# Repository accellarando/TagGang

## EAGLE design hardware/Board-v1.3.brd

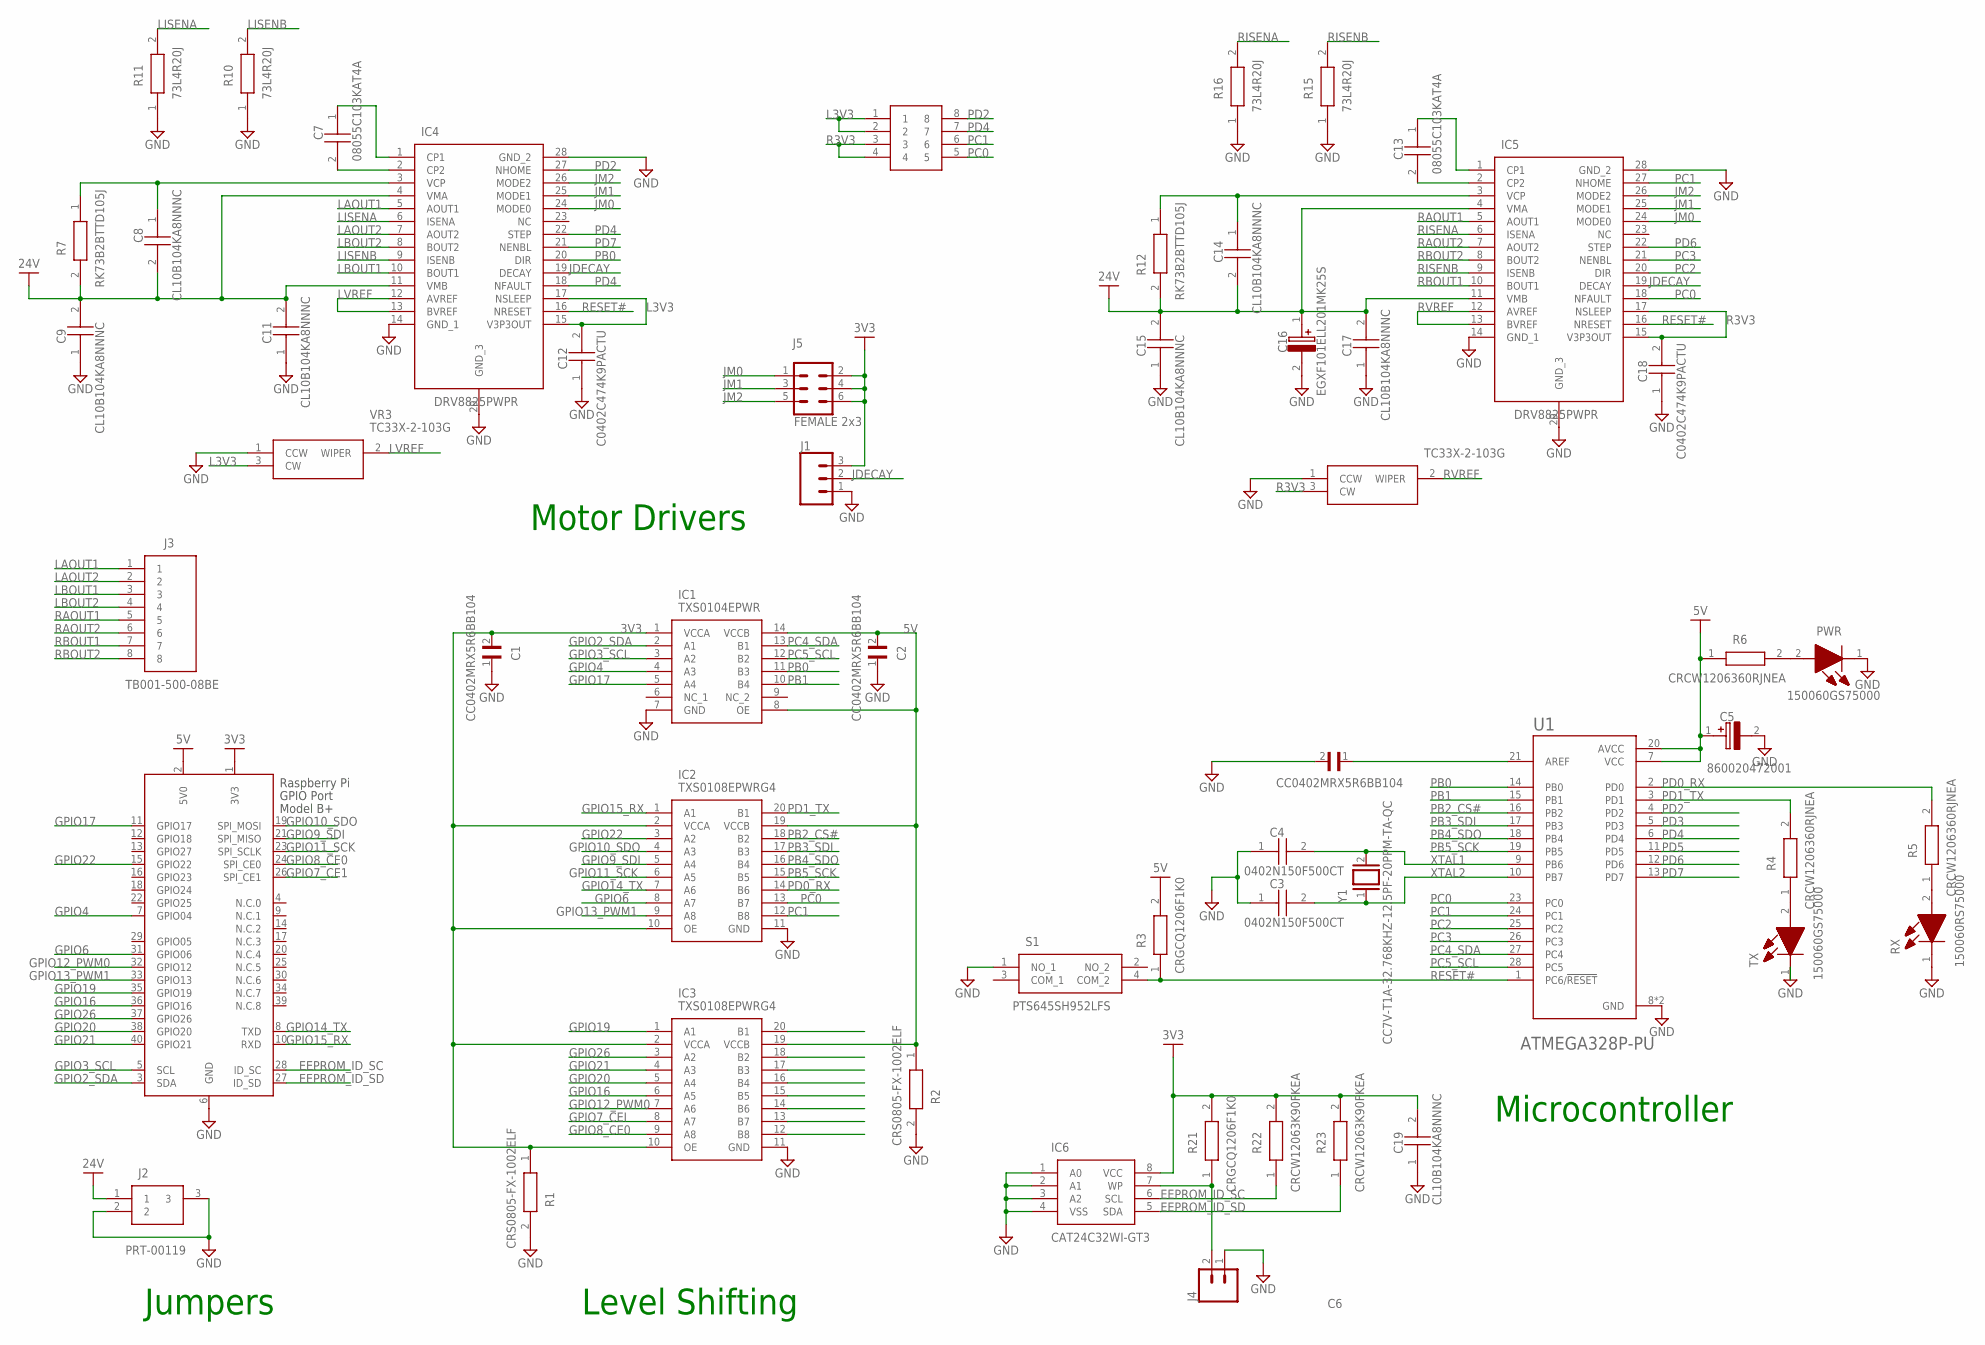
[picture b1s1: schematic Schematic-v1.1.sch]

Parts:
C1, C2, C6: CC0402MRX5R6BB104; CAPC1005X55N
C3, C4: 0402N150F500CT; CAPC1005X55N
C5: 860020472001; CAPPRD200W52D500H1250
C7, C13: 08055C103KAT4A; CAPC2012X94N
C8, C9, C11, C14, C15, C17, C19: CL10B104KA8NNNC; CAPC1608X90N
C12, C18: C0402C474K9PACTU; CAPC1005X55N
C16: EGXF101ELL201MK25S; CAPPRD500W60D1275H2650
IC1: TXS0104EPWR; SOP65P640X120-14N
IC2, IC3: TXS0108EPWRG4; SOP65P640X120-20N
IC4, IC5: DRV8825PWPR; SOP65P640X120-29N
IC6: CAT24C32WI-GT3; SOIC127P600X175-8N
J1: CONN_03; 1X03
J2: PRT-00119; PRT00119
J3: TB001-500-08BE; TB00150008BE
J4: CONN_02; 1X02
J5: FEMALE 2x3; 2X3
PWR: 150060GS75000; LEDC1608X80N
R1, R2: CRS0805-FX-1002ELF; RESC2012X60N
R3, R21: CRGCQ1206F1K0; RESC3116X65N
R4, R5, R6: CRCW1206360RJNEA; RESC3216X60N
R7, R12: RK73B2BTTD105J; RESC3216X70N
R10, R11, R15, R16: 73L4R20J; RESC3216X70N
R22, R23: CRCW12063K90FKEA; RESC3216X60N
RN1: YC124-JR-0710KL; YC124JR0710KL
RX: 150060RS75000; LEDC1608X80N
S1: PTS645SH952LFS
TX: 150060GS75000; LEDC1608X80N
U1: ATMEGA328P-PU; DIP794W46P254L2967H457Q28B
VR3, VR4: TC33X-2-103G; TC33X2503E
X1: RASPI_BOARD_B+_HD; RASPI_BOARD_B+HAT_DF
Y1: CC7V-T1A-32.768KHZ-12.5PF-20PPM-TA-QC; XTAL_CC7V-T1A-32.768KHZ-12.5PF-20PPM-TA-QC

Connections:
24V: C8.2, C9.2, C11.2, C14.2, C15.2, C16.1 (+), C17.2, IC4.4 (VMA), IC4.11 (VMB), IC5.4 (VMA), IC5.11 (VMB), J2.1, R7.2, R12.2
EEPROM_ID_SC: IC6.6 (SCL), R22.1, X1.28 (ID_SC)
EEPROM_ID_SD: IC6.5 (SDA), R23.1, X1.27 (ID_SD)
GND: C1.1, C2.1, C3.1, C4.1, C5.2 (-), C6.2, C9.1, C11.1, C12.1, C15.1, C16.2 (-), C17.1, C18.1, C19.1, IC1.7 (GND), IC2.11 (GND), IC3.11 (GND), IC4.14 (GND_1), IC4.28 (GND_2), IC4.29 (GND_3), IC5.14 (GND_1), IC5.28 (GND_2), IC5.29 (GND_3), IC6.1 (A0), IC6.2 (A1), IC6.3 (A2), IC6.4 (VSS), J1.1, J2.2, J2.3, J4.1, PWR.1 (K), R1.2, R2.2, R10.1, R11.1, R15.1, R16.1, RX.1 (K), S1.1 (NO_1), TX.1 (K), U1.8 (GND), U1.22 (GND), VR3.1 (CCW), VR4.1 (CCW), X1.6 (GND); also elsewhere on the board
GPIO2_SDA: IC1.2 (A1), X1.3 (SDA)
GPIO3_SCL: IC1.3 (A2), X1.5 (SCL)
GPIO4: IC1.4 (A3), X1.7 (GPIO04)
GPIO6: IC2.8 (A7), X1.31 (GPIO06)
GPIO7_CE1: X1.26 (SPI_CE1)
GPIO7_CEI: IC3.8 (A7)
GPIO8_CE0: IC3.9 (A8), X1.24 (SPI_CE0)
GPIO9_SDI: IC2.5 (A4), X1.21 (SPI_MISO)
GPIO10_SDO: IC2.4 (A3), X1.19 (SPI_MOSI)
GPIO11_SCK: IC2.6 (A5), X1.23 (SPI_SCLK)
GPIO12_PWM0: IC3.7 (A6), X1.32 (GPIO12)
GPIO13_PWM1: IC2.9 (A8), X1.33 (GPIO13)
GPIO14_TX: IC2.7 (A6), X1.8 (TXD)
GPIO15_RX: IC2.1 (A1), X1.10 (RXD)
GPIO16: IC3.6 (A5), X1.36 (GPIO16)
GPIO17: IC1.5 (A4), X1.11 (GPIO17)
GPIO19: IC3.1 (A1), X1.35 (GPIO19)
GPIO20: IC3.5 (A4), X1.38 (GPIO20)
GPIO21: IC3.4 (A3), X1.40 (GPIO21)
GPIO22: IC2.3 (A2), X1.15 (GPIO22)
GPIO26: IC3.3 (A2), X1.37 (GPIO26)
JDECAY: IC4.19 (DECAY), IC5.19 (DECAY), J1.2; also elsewhere on the board
JM2: IC4.26 (MODE2), IC5.26 (MODE2), J5.5; also elsewhere on the board
L3V3: C12.2, IC4.15 (V3P3OUT), IC4.17 (NSLEEP), RN1.1, RN1.2, VR3.3 (CW)
LAOUT1: IC4.5 (AOUT1), J3.1
LAOUT2: IC4.7 (AOUT2), J3.2
LBOUT1: IC4.10 (BOUT1), J3.3
LBOUT2: IC4.8 (BOUT2), J3.4
LISENA: IC4.6 (ISENA), R11.2
LISENB: IC4.9 (ISENB), R10.2
LVREF: IC4.12 (AVREF), IC4.13 (BVREF), VR3.2 (WIPER)
unnamed: C13.1, IC5.1 (CP1)
unnamed: R5.1, RX.2 (A)
unnamed: PWR.2 (A), R6.2
unnamed: C6.1, U1.21 (AREF)
unnamed: C7.1, IC4.1 (CP1)
unnamed: C7.2, IC4.2 (CP2)
unnamed: C13.2, IC5.2 (CP2)
unnamed: C8.1, IC4.3 (VCP), R7.1
unnamed: C14.1, IC5.3 (VCP), R12.1
unnamed: R4.1, TX.2 (A)
unnamed: IC6.7 (WP), J4.2, R21.1
PB0: IC1.11 (B3), IC4.20 (DIR), U1.14 (PB0)
PB1: IC1.10 (B4), U1.15 (PB1)
PB2_CS#: IC2.18 (B2), U1.16 (PB2)
PB3_SDI: IC2.17 (B3), U1.17 (PB3)
PB4_SDO: IC2.16 (B4), U1.18 (PB4)
PB5_SCK: IC2.15 (B5), U1.19 (PB5)
PC2: IC5.20 (DIR), U1.25 (PC2)
PC3: IC5.21 (NENBL), U1.26 (PC3)
PC4_SDA: IC1.13 (B1), U1.27 (PC4)
PC5_SCL: IC1.12 (B2), U1.28 (PC5)
PD0_RX: IC2.14 (B6), R5.2, U1.2 (PD0)
PD1_TX: IC2.20 (B1), R4.2, U1.3 (PD1)
PD3: U1.5 (PD3)
PD5: U1.11 (PD5)
PD6: IC5.22 (STEP), U1.12 (PD6)
PD7: IC4.21 (NENBL), U1.13 (PD7)
R3V3: C18.2, IC5.15 (V3P3OUT), IC5.17 (NSLEEP), RN1.3, RN1.4, VR4.3 (CW)
RAOUT1: IC5.5 (AOUT1), J3.5
RAOUT2: IC5.7 (AOUT2), J3.6
RBOUT1: IC5.10 (BOUT1), J3.7
RBOUT2: IC5.8 (BOUT2), J3.8
RESET#: IC4.16 (NRESET), IC5.16 (NRESET), R3.1, S1.4 (COM_2), U1.1 (PC6/!RESET)
RISENA: IC5.6 (ISENA), R16.2
RISENB: IC5.9 (ISENB), R15.2
RVREF: IC5.12 (AVREF), IC5.13 (BVREF), VR4.2 (WIPER)
XTAL1: C4.2, U1.9 (PB6), Y1.2
XTAL2: C3.2, U1.10 (PB7), Y1.1

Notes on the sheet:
Jumpers
Level Shifting
Microcontroller
Motor Drivers

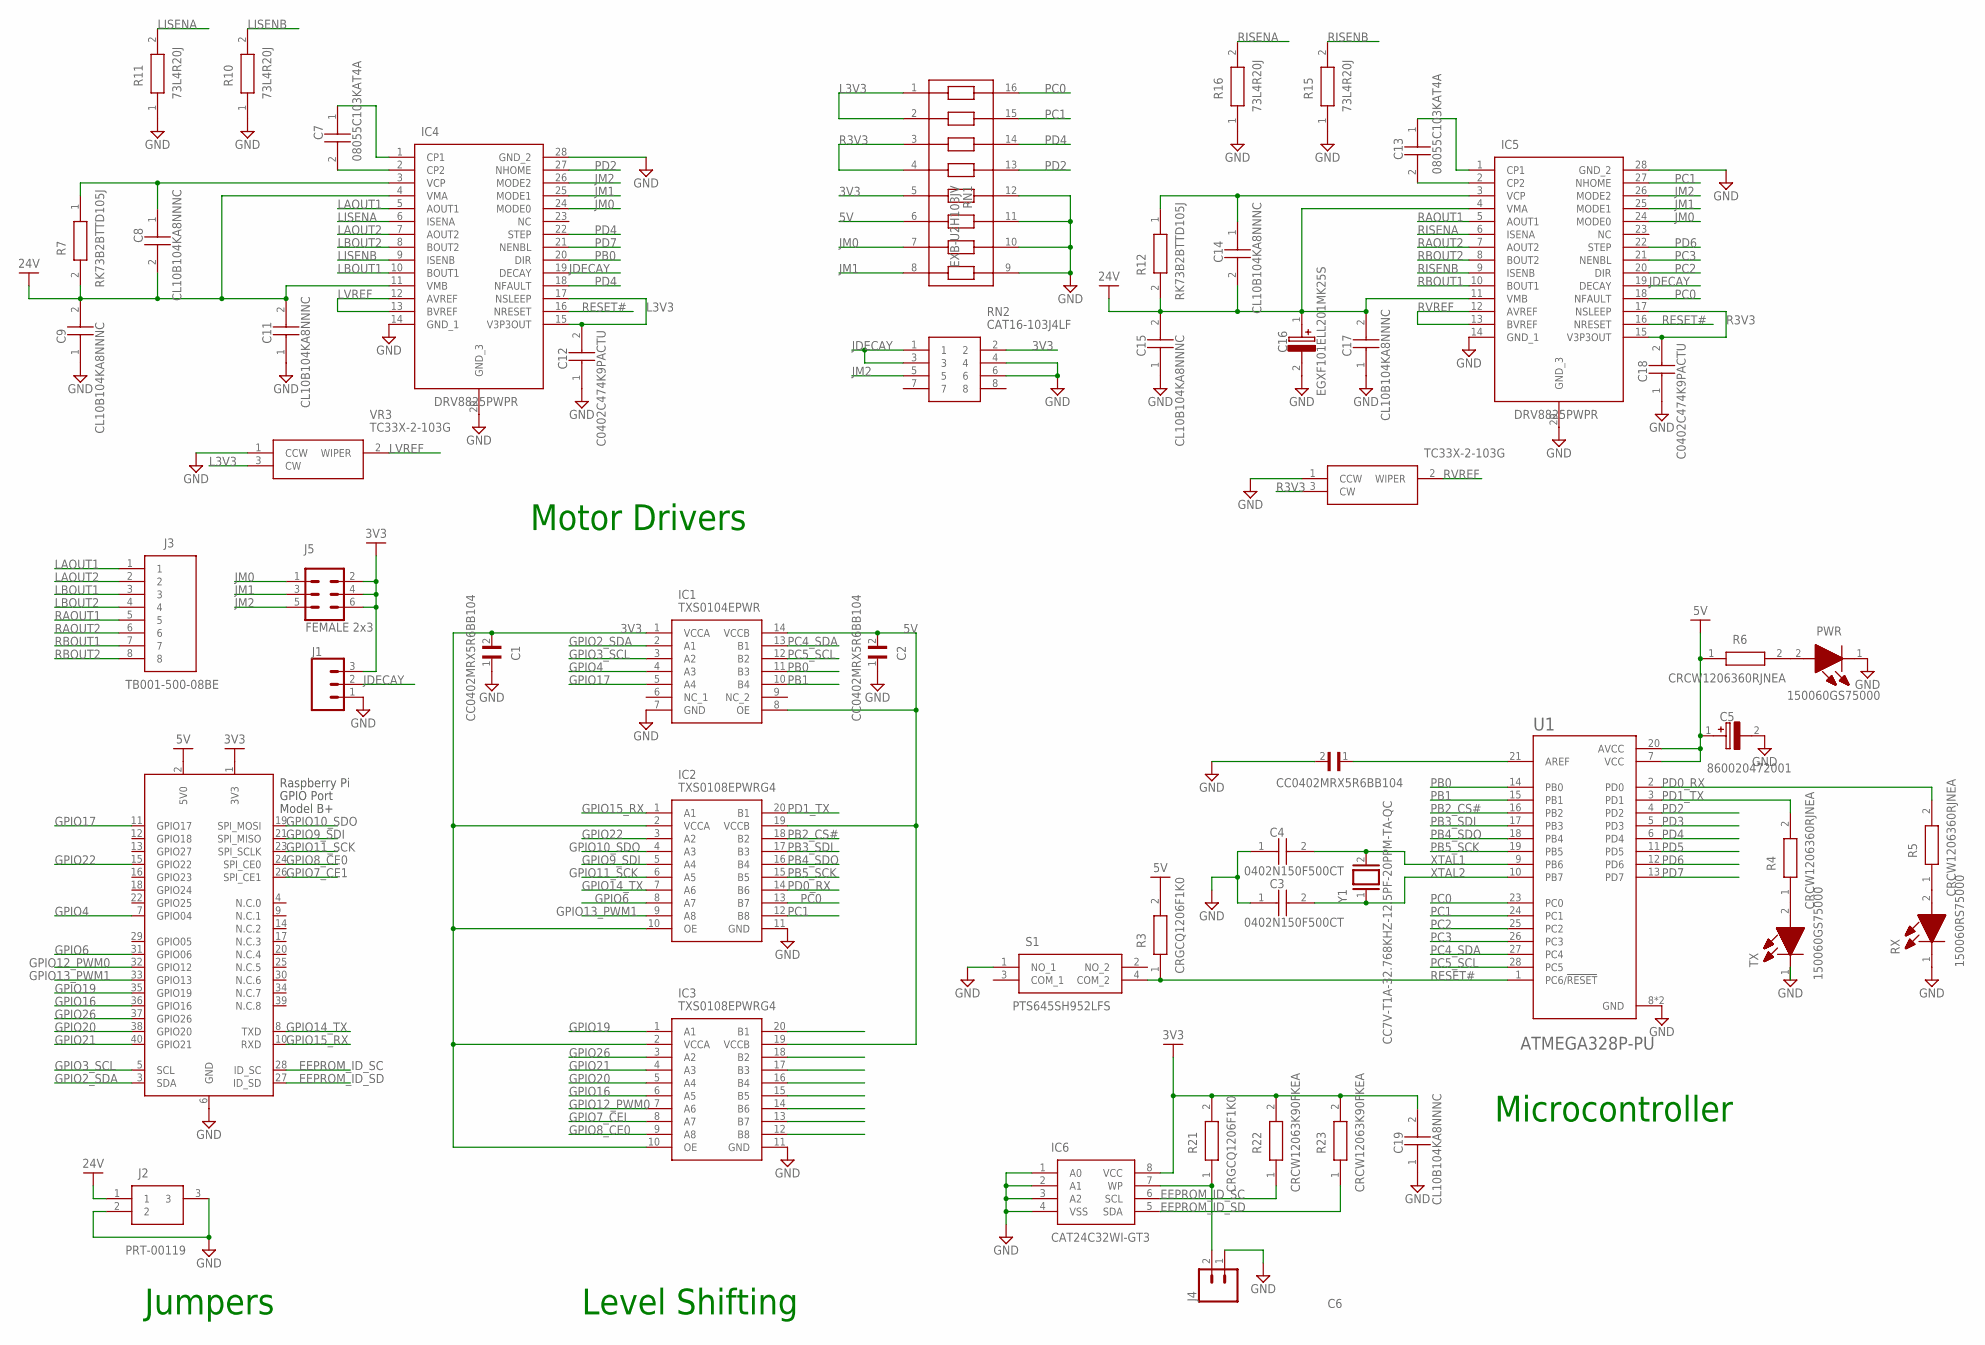
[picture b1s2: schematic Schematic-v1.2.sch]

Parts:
C1, C2, C6: CC0402MRX5R6BB104; CAPC1005X55N
C3, C4: 0402N150F500CT; CAPC1005X55N
C5: 860020472001; CAPPRD200W52D500H1250
C7, C13: 08055C103KAT4A; CAPC2012X94N
C8, C9, C11, C14, C15, C17, C19: CL10B104KA8NNNC; CAPC1608X90N
C12, C18: C0402C474K9PACTU; CAPC1005X55N
C16: EGXF101ELL201MK25S; CAPPRD500W60D1275H2650
IC1: TXS0104EPWR; SOP65P640X120-14N
IC2, IC3: TXS0108EPWRG4; SOP65P640X120-20N
IC4, IC5: DRV8825PWPR; SOP65P640X120-29N
IC6: CAT24C32WI-GT3; SOIC127P600X175-8N
J1: CONN_03; 1X03
J2: PRT-00119; PRT00119
J3: TB001-500-08BE; TB00150008BE
J4: CONN_02; 1X02
J5: FEMALE 2x3; 2X3
PWR: 150060GS75000; LEDC1608X80N
R3, R21: CRGCQ1206F1K0; RESC3116X65N
R4, R5, R6: CRCW1206360RJNEA; RESC3216X60N
R7, R12: RK73B2BTTD105J; RESC3216X70N
R10, R11, R15, R16: 73L4R20J; RESC3216X70N
R22, R23: CRCW12063K90FKEA; RESC3216X60N
RN1: EXB-U2H103JV; EXBU2H
RN2: CAT16-103J4LF; CAPCAV80P155X320X60-8L
RX: 150060RS75000; LEDC1608X80N
S1: PTS645SH952LFS
TX: 150060GS75000; LEDC1608X80N
U1: ATMEGA328P-PU; DIP794W46P254L2967H457Q28B
VR3, VR4: TC33X-2-103G; TC33X2503E
X1: RASPI_BOARD_B+_HD; RASPI_BOARD_B+HAT_DF
Y1: CC7V-T1A-32.768KHZ-12.5PF-20PPM-TA-QC; XTAL_CC7V-T1A-32.768KHZ-12.5PF-20PPM-TA-QC

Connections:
24V: C8.2, C9.2, C11.2, C14.2, C15.2, C16.1 (+), C17.2, IC4.4 (VMA), IC4.11 (VMB), IC5.4 (VMA), IC5.11 (VMB), J2.1, R7.2, R12.2
EEPROM_ID_SC: IC6.6 (SCL), R22.1, X1.28 (ID_SC)
EEPROM_ID_SD: IC6.5 (SDA), R23.1, X1.27 (ID_SD)
GND: C1.1, C2.1, C3.1, C4.1, C5.2 (-), C6.2, C9.1, C11.1, C12.1, C15.1, C16.2 (-), C17.1, C18.1, C19.1, IC1.7 (GND), IC2.11 (GND), IC3.11 (GND), IC4.14 (GND_1), IC4.28 (GND_2), IC4.29 (GND_3), IC5.14 (GND_1), IC5.28 (GND_2), IC5.29 (GND_3), IC6.1 (A0), IC6.2 (A1), IC6.3 (A2), IC6.4 (VSS), J1.1, J2.2, J2.3, J4.1, PWR.1 (K), R10.1, R11.1, R15.1, R16.1, RN1.9, RN1.10, RN1.11, RN1.12, RN2.4, RN2.6, RX.1 (K), S1.1 (NO_1), TX.1 (K), U1.8 (GND), U1.22 (GND), VR3.1 (CCW), VR4.1 (CCW), X1.6 (GND); also elsewhere on the board
GPIO2_SDA: IC1.2 (A1), X1.3 (SDA)
GPIO3_SCL: IC1.3 (A2), X1.5 (SCL)
GPIO4: IC1.4 (A3), X1.7 (GPIO04)
GPIO6: IC2.8 (A7), X1.31 (GPIO06)
GPIO7_CE1: X1.26 (SPI_CE1)
GPIO7_CEI: IC3.8 (A7)
GPIO8_CE0: IC3.9 (A8), X1.24 (SPI_CE0)
GPIO9_SDI: IC2.5 (A4), X1.21 (SPI_MISO)
GPIO10_SDO: IC2.4 (A3), X1.19 (SPI_MOSI)
GPIO11_SCK: IC2.6 (A5), X1.23 (SPI_SCLK)
GPIO12_PWM0: IC3.7 (A6), X1.32 (GPIO12)
GPIO13_PWM1: IC2.9 (A8), X1.33 (GPIO13)
GPIO14_TX: IC2.7 (A6), X1.8 (TXD)
GPIO15_RX: IC2.1 (A1), X1.10 (RXD)
GPIO16: IC3.6 (A5), X1.36 (GPIO16)
GPIO17: IC1.5 (A4), X1.11 (GPIO17)
GPIO19: IC3.1 (A1), X1.35 (GPIO19)
GPIO20: IC3.5 (A4), X1.38 (GPIO20)
GPIO21: IC3.4 (A3), X1.40 (GPIO21)
GPIO22: IC2.3 (A2), X1.15 (GPIO22)
GPIO26: IC3.3 (A2), X1.37 (GPIO26)
JDECAY: IC4.19 (DECAY), IC5.19 (DECAY), J1.2, RN2.1, RN2.3
JM2: IC4.26 (MODE2), IC5.26 (MODE2), J5.5, RN2.5
L3V3: C12.2, IC4.15 (V3P3OUT), IC4.17 (NSLEEP), RN1.1, RN1.2, VR3.3 (CW)
LAOUT1: IC4.5 (AOUT1), J3.1
LAOUT2: IC4.7 (AOUT2), J3.2
LBOUT1: IC4.10 (BOUT1), J3.3
LBOUT2: IC4.8 (BOUT2), J3.4
LISENA: IC4.6 (ISENA), R11.2
LISENB: IC4.9 (ISENB), R10.2
LVREF: IC4.12 (AVREF), IC4.13 (BVREF), VR3.2 (WIPER)
unnamed: C13.1, IC5.1 (CP1)
unnamed: R5.1, RX.2 (A)
unnamed: PWR.2 (A), R6.2
unnamed: C6.1, U1.21 (AREF)
unnamed: C7.1, IC4.1 (CP1)
unnamed: C7.2, IC4.2 (CP2)
unnamed: C13.2, IC5.2 (CP2)
unnamed: C8.1, IC4.3 (VCP), R7.1
unnamed: C14.1, IC5.3 (VCP), R12.1
unnamed: R4.1, TX.2 (A)
unnamed: IC6.7 (WP), J4.2, R21.1
PB0: IC1.11 (B3), IC4.20 (DIR), U1.14 (PB0)
PB1: IC1.10 (B4), U1.15 (PB1)
PB2_CS#: IC2.18 (B2), U1.16 (PB2)
PB3_SDI: IC2.17 (B3), U1.17 (PB3)
PB4_SDO: IC2.16 (B4), U1.18 (PB4)
PB5_SCK: IC2.15 (B5), U1.19 (PB5)
PC2: IC5.20 (DIR), U1.25 (PC2)
PC3: IC5.21 (NENBL), U1.26 (PC3)
PC4_SDA: IC1.13 (B1), U1.27 (PC4)
PC5_SCL: IC1.12 (B2), U1.28 (PC5)
PD0_RX: IC2.14 (B6), R5.2, U1.2 (PD0)
PD1_TX: IC2.20 (B1), R4.2, U1.3 (PD1)
PD3: U1.5 (PD3)
PD5: U1.11 (PD5)
PD6: IC5.22 (STEP), U1.12 (PD6)
PD7: IC4.21 (NENBL), U1.13 (PD7)
R3V3: C18.2, IC5.15 (V3P3OUT), IC5.17 (NSLEEP), RN1.3, RN1.4, VR4.3 (CW)
RAOUT1: IC5.5 (AOUT1), J3.5
RAOUT2: IC5.7 (AOUT2), J3.6
RBOUT1: IC5.10 (BOUT1), J3.7
RBOUT2: IC5.8 (BOUT2), J3.8
RESET#: IC4.16 (NRESET), IC5.16 (NRESET), R3.1, S1.4 (COM_2), U1.1 (PC6/!RESET)
RISENA: IC5.6 (ISENA), R16.2
RISENB: IC5.9 (ISENB), R15.2
RVREF: IC5.12 (AVREF), IC5.13 (BVREF), VR4.2 (WIPER)
XTAL1: C4.2, U1.9 (PB6), Y1.2
XTAL2: C3.2, U1.10 (PB7), Y1.1

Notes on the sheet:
Jumpers
Level Shifting
Microcontroller
Motor Drivers

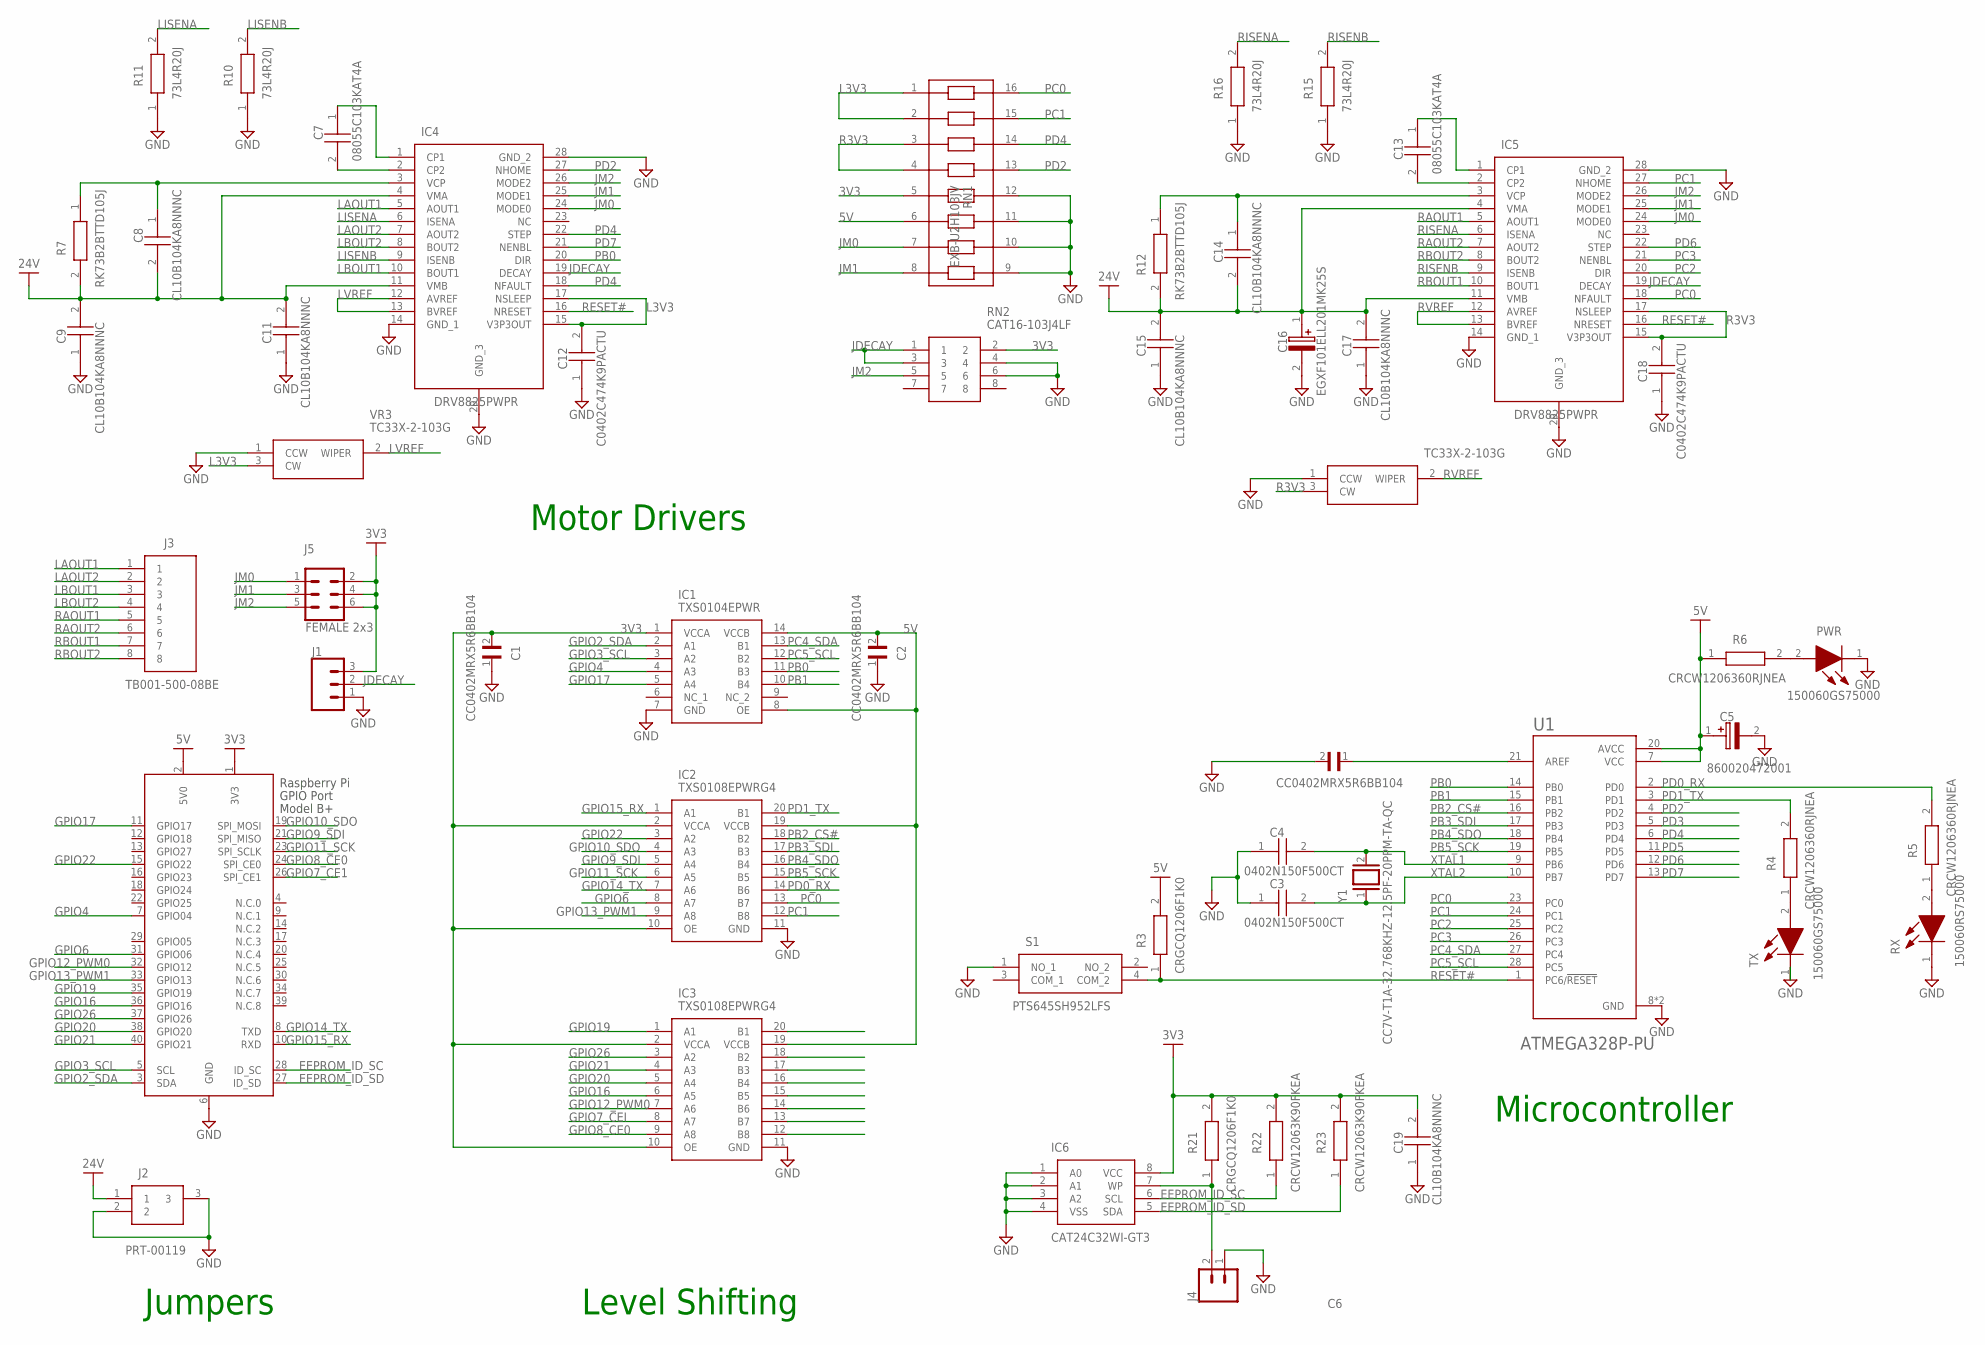
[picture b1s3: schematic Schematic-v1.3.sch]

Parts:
C1, C2, C6: CC0402MRX5R6BB104; CAPC1005X55N
C3, C4: 0402N150F500CT; CAPC1005X55N
C5: 860020472001; CAPPRD200W52D500H1250
C7, C13: 08055C103KAT4A; CAPC2012X94N
C8, C9, C11, C14, C15, C17, C19: CL10B104KA8NNNC; CAPC1608X90N
C12, C18: C0402C474K9PACTU; CAPC1005X55N
C16: EGXF101ELL201MK25S; CAPPRD500W60D1275H2650
IC1: TXS0104EPWR; SOP65P640X120-14N
IC2, IC3: TXS0108EPWRG4; SOP65P640X120-20N
IC4, IC5: DRV8825PWPR; SOP65P640X120-29N
IC6: CAT24C32WI-GT3; SOIC127P600X175-8N
J1: CONN_03; 1X03
J2: PRT-00119; PRT00119
J3: TB001-500-08BE; TB00150008BE
J4: CONN_02; 1X02
J5: FEMALE 2x3; 2X3
PWR: 150060GS75000; LEDC1608X80N
R3, R21: CRGCQ1206F1K0; RESC3116X65N
R4, R5, R6: CRCW1206360RJNEA; RESC3216X60N
R7, R12: RK73B2BTTD105J; RESC3216X70N
R10, R11, R15, R16: 73L4R20J; RESC3216X70N
R22, R23: CRCW12063K90FKEA; RESC3216X60N
RN1: EXB-U2H103JV; EXBU2H
RN2: CAT16-103J4LF; CAPCAV80P155X320X60-8L
RX: 150060RS75000; LEDC1608X80N
S1: PTS645SH952LFS
TX: 150060GS75000; LEDC1608X80N
U1: ATMEGA328P-PU; DIP794W46P254L2967H457Q28B
VR3, VR4: TC33X-2-103G; TC33X2503E
X1: RASPI_BOARD_B+_HD; RASPI_BOARD_B+HAT_DF
Y1: CC7V-T1A-32.768KHZ-12.5PF-20PPM-TA-QC; XTAL_CC7V-T1A-32.768KHZ-12.5PF-20PPM-TA-QC

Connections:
24V: C8.2, C9.2, C11.2, C14.2, C15.2, C16.1 (+), C17.2, IC4.4 (VMA), IC4.11 (VMB), IC5.4 (VMA), IC5.11 (VMB), J2.1, R7.2, R12.2
EEPROM_ID_SC: IC6.6 (SCL), R22.1, X1.28 (ID_SC)
EEPROM_ID_SD: IC6.5 (SDA), R23.1, X1.27 (ID_SD)
GND: C1.1, C2.1, C3.1, C4.1, C5.2 (-), C6.2, C9.1, C11.1, C12.1, C15.1, C16.2 (-), C17.1, C18.1, C19.1, IC1.7 (GND), IC2.11 (GND), IC3.11 (GND), IC4.14 (GND_1), IC4.28 (GND_2), IC4.29 (GND_3), IC5.14 (GND_1), IC5.28 (GND_2), IC5.29 (GND_3), IC6.1 (A0), IC6.2 (A1), IC6.3 (A2), IC6.4 (VSS), J1.1, J2.2, J2.3, J4.1, PWR.1 (K), R10.1, R11.1, R15.1, R16.1, RN1.9, RN1.10, RN1.11, RN1.12, RN2.4, RN2.6, RX.1 (K), S1.1 (NO_1), TX.1 (K), U1.8 (GND), U1.22 (GND), VR3.1 (CCW), VR4.1 (CCW), X1.6 (GND); also elsewhere on the board
GPIO2_SDA: IC1.2 (A1), X1.3 (SDA)
GPIO3_SCL: IC1.3 (A2), X1.5 (SCL)
GPIO4: IC1.4 (A3), X1.7 (GPIO04)
GPIO6: IC2.8 (A7), X1.31 (GPIO06)
GPIO7_CE1: X1.26 (SPI_CE1)
GPIO7_CEI: IC3.8 (A7)
GPIO8_CE0: IC3.9 (A8), X1.24 (SPI_CE0)
GPIO9_SDI: IC2.5 (A4), X1.21 (SPI_MISO)
GPIO10_SDO: IC2.4 (A3), X1.19 (SPI_MOSI)
GPIO11_SCK: IC2.6 (A5), X1.23 (SPI_SCLK)
GPIO12_PWM0: IC3.7 (A6), X1.32 (GPIO12)
GPIO13_PWM1: IC2.9 (A8), X1.33 (GPIO13)
GPIO14_TX: IC2.7 (A6), X1.8 (TXD)
GPIO15_RX: IC2.1 (A1), X1.10 (RXD)
GPIO16: IC3.6 (A5), X1.36 (GPIO16)
GPIO17: IC1.5 (A4), X1.11 (GPIO17)
GPIO19: IC3.1 (A1), X1.35 (GPIO19)
GPIO20: IC3.5 (A4), X1.38 (GPIO20)
GPIO21: IC3.4 (A3), X1.40 (GPIO21)
GPIO22: IC2.3 (A2), X1.15 (GPIO22)
GPIO26: IC3.3 (A2), X1.37 (GPIO26)
JDECAY: IC4.19 (DECAY), IC5.19 (DECAY), J1.2, RN2.1, RN2.3
JM2: IC4.26 (MODE2), IC5.26 (MODE2), J5.5, RN2.5
L3V3: C12.2, IC4.15 (V3P3OUT), IC4.17 (NSLEEP), RN1.1, RN1.2, VR3.3 (CW)
LAOUT1: IC4.5 (AOUT1), J3.1
LAOUT2: IC4.7 (AOUT2), J3.2
LBOUT1: IC4.10 (BOUT1), J3.3
LBOUT2: IC4.8 (BOUT2), J3.4
LISENA: IC4.6 (ISENA), R11.2
LISENB: IC4.9 (ISENB), R10.2
LVREF: IC4.12 (AVREF), IC4.13 (BVREF), VR3.2 (WIPER)
unnamed: C13.1, IC5.1 (CP1)
unnamed: R5.1, RX.2 (A)
unnamed: PWR.2 (A), R6.2
unnamed: C6.1, U1.21 (AREF)
unnamed: C7.1, IC4.1 (CP1)
unnamed: C7.2, IC4.2 (CP2)
unnamed: C13.2, IC5.2 (CP2)
unnamed: C8.1, IC4.3 (VCP), R7.1
unnamed: C14.1, IC5.3 (VCP), R12.1
unnamed: R4.1, TX.2 (A)
unnamed: IC6.7 (WP), J4.2, R21.1
PB0: IC1.11 (B3), IC4.20 (DIR), U1.14 (PB0)
PB1: IC1.10 (B4), U1.15 (PB1)
PB2_CS#: IC2.18 (B2), U1.16 (PB2)
PB3_SDI: IC2.17 (B3), U1.17 (PB3)
PB4_SDO: IC2.16 (B4), U1.18 (PB4)
PB5_SCK: IC2.15 (B5), U1.19 (PB5)
PC2: IC5.20 (DIR), U1.25 (PC2)
PC3: IC5.21 (NENBL), U1.26 (PC3)
PC4_SDA: IC1.13 (B1), U1.27 (PC4)
PC5_SCL: IC1.12 (B2), U1.28 (PC5)
PD0_RX: IC2.14 (B6), R5.2, U1.2 (PD0)
PD1_TX: IC2.20 (B1), R4.2, U1.3 (PD1)
PD3: U1.5 (PD3)
PD5: U1.11 (PD5)
PD6: IC5.22 (STEP), U1.12 (PD6)
PD7: IC4.21 (NENBL), U1.13 (PD7)
R3V3: C18.2, IC5.15 (V3P3OUT), IC5.17 (NSLEEP), RN1.3, RN1.4, VR4.3 (CW)
RAOUT1: IC5.5 (AOUT1), J3.5
RAOUT2: IC5.7 (AOUT2), J3.6
RBOUT1: IC5.10 (BOUT1), J3.7
RBOUT2: IC5.8 (BOUT2), J3.8
RESET#: IC4.16 (NRESET), IC5.16 (NRESET), R3.1, S1.4 (COM_2), U1.1 (PC6/!RESET)
RISENA: IC5.6 (ISENA), R16.2
RISENB: IC5.9 (ISENB), R15.2
RVREF: IC5.12 (AVREF), IC5.13 (BVREF), VR4.2 (WIPER)
XTAL1: C4.2, U1.9 (PB6), Y1.2
XTAL2: C3.2, U1.10 (PB7), Y1.1

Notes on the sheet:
Jumpers
Level Shifting
Microcontroller
Motor Drivers

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
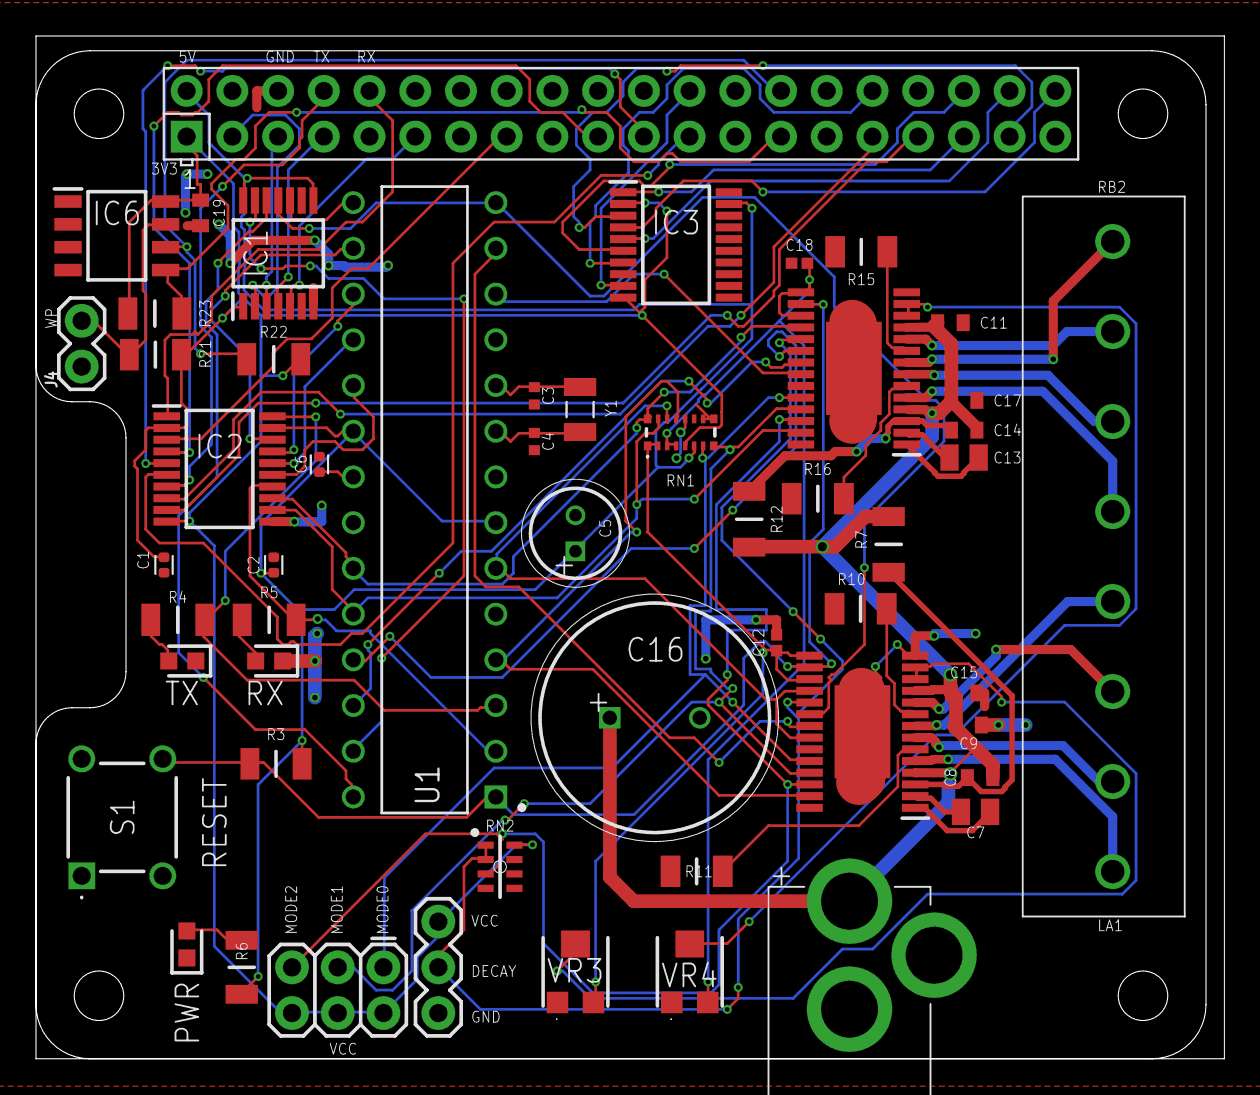
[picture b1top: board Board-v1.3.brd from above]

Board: 2 copper layers, 66.0 x 56.8 mm, 53 parts (0 on the bottom side), 77 nets.

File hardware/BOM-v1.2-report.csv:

"Qty","Model Number","Parts","DESCRIPTION","Price","Total Cost"
1,"CONN_02","J4","2x1 pin header",,0
1,"CONN_03","J1","3x1 pin header",,0
2,"0402N150F500CT","C3, C4","SMD Ceramic Capacitor, 0402 MLCC NPO 15 pF +/- 1% 50 V",$0.10,$0.20
2,"08055C103KAT4A","C7, C13","SMD Ceramic Capacitor, 50V .01uF X7R 0805 10%TOL",$0.10,$0.20
2,"150060GS75000","PWR, TX","520 nm Green LED, 1608 (0603) Clear SMD package",0.15,0.3
1,"150060RS75000","RX","LED, 0603, RED, 250MCD, 625NM",$0.15,$0.15
4,"73L4R20J","R10, R11, R15, R16","Current Sense Resistor - SMD 0.2ohms 5%",$0.21,$0.84
1,860020472001,"C5","4.7uF 25 VDC Aluminium Electrolytic Capacitor",$0.10,$0.10
1,"ATMEGA328P-PU","U1","Arduino ATMEGA328P Microcontroller",$2.97,$2.97
2,"C0402C474K9PACTU","C12, C18","SMD Comm X5R, Ceramic Capacitor, 0.47 uF, 10%, 6.3 VDC, 15.75 VDC, 0402, ",$0.10,$0.20
1,"CAT24C32WI-GT3","IC6","EEPROM Serial-I2C 32K 4Kx8 1.8V/5V SOIC8 CAT24C32WI-GT3, 8-Pin SOIC",$0.37,$0.37
3,"CC0402MRX5R6BB104","C1, C2, C6"," 0.1 µF ±20% 10V Ceramic Capacitor X5R 0402 (1005 Metric) ","0.12 for 10",$0.12
1,"CC7V-T1A-16.384KHZ-12.5PF-20PPM-TA-QC","Y1"," LOW FREQUENCY CRYSTAL ",$0.71,$0.71
7,"CL10B104KA8NNNC","C8, C9, C11, C14, C15, C17, C19","Ceramic capacitor 0603 X7R 25V 100nF (MLCC) 25 V +/-10% X7R dielectric CL","$0.14 for 10",$0.14
3,"CRCW1206360RJNEA","R4, R5, R6","Thick Film Resistors - SMD 1/4watt 360ohms 5%",0.1,0.3
2,"CRCW12063K90FKEA","R22, R23","Thick Film Surface Mount Resistor 1206 Case 3.9k +/-1% 0.25W",0.1,0.2
2,"CRGCQ1206F1K0","R3, R21","SMD AEC-Q200 Compliant Thick Film Chip Resistor",0.1,0.2
2,"DRV8825PWPR","IC4, IC5","2.5A Bipolar Stepper Motor Driver with On-Chip 1/32 Microstepping Indexer (Step/Dir Ctrl)",5.57,11.14
1,"EGXF101ELL201MK25S","C16","Aluminum Electrolytic Capacitors - Radial Leaded 200uF 100 Volts 20%",2.41,2.41
1,"EXB-U2H103JV","RN1","Resistor Array 8 x 10k, Power Rating (W): 1/16 W, 5%",0.41,0.41
1,"CAT16-103J4LF","RN2","4x 10k Resistor Network",0.1,0.1
1,"FEMALE 2x3","J5","2x3 pin header",,0
1,"PRT-00119","J2","SparkFun Accessories DC Barrel Power Jack/Connector",1.25,1.25
1,"PTS645SH952LFS","S1","SWITCH TACTILE SPST-NO 0.05A 12V",0.23,0.23
1,"RASPI_BOARD_B+_HD","X1","Raspberry Pi GPIO Connector",1.94,1.94
2,"RK73B2BTTD105J","R7, R12","Thick Film Resistors - SMD 1/4watts 1Mohms 5%",0.1,0.2
1,"TB001-500-08BE","J3","Terminal block, screw type, 5.00 , horizontal, 8 poles, CUI Blue, slotted screw, PCB mount",1.29,1.29
2,"TC33X-2-103G","VR3, VR4","Trimmer Resistors - SMD 3MM 10KOHMS 25% 0.1WATT",0.28,0.56
1,"TXS0104EPWR","IC1","Voltage Level Translator, Open Drain 1.65  3.6 V, 2.3  5.5 V 14-Pin TSSOP",1.15,1.15
2,"TXS0108EPWRG4","IC2, IC3","Voltage Level Translator, 8B Bidir Vltg-Level Translator",1.53,3.06
,,,,"TOTAL:",30.74

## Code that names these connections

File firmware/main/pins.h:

/**
 * This file contains pin definitions for the TagGang
 * Arduino Pi HAT.
 */
#ifndef PINS_H
#define PINS_H

#include <Arduino.h>

// Left motor-driver pins
#define PIN_L_NFAULT	PD4
#define PIN_L_DIR	    PB0
#define PIN_L_NENBL		PD7
#define PIN_L_STEP		PD5
#define PIN_L_NHOME		PD2

// Right motor-driver pins
#define PIN_R_NFAULT	PC0
#define PIN_R_DIR		PC2
#define PIN_R_NENBL		PC3
#define PIN_R_STEP		PD6
#define PIN_R_NHOME		PC1

#define PIN_PEN_SERVO   PB1

#endif

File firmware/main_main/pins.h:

// Pins
#define STEP_PIN_L		PB2 // PD5 net on board
#define DIR_PIN_L		PB4 // PB0 net on board
#define ENABLE_PIN_L	PB5 // PD7 net on board

// These pins are on the NUCLEO driver
#define STEP_PIN_R		PD6
#define DIR_PIN_R		  PD7
#define ENABLE_PIN_R	PD2
#define CTR_PIN       PD5
#define RST_PIN       PB0
#define REFA_PIN      PD3
#define REFB_PIN      PB1

#define PIN_PEN_SERVO A2

// Stepper motor constants
#define GEAR_RADIUS 4.0 //mm
#define DEGREES_PER_STEP 1.8
#define PULSES_PER_STEP 1.0
#define STEPS_PER_MM ((180.0*PULSES_PER_STEP) / (PI * GEAR_RADIUS * DEGREES_PER_STEP))
#define STEPS(x) (x*STEPS_PER_MM)

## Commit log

2023-03-02 website test
2023-03-02 renamed website dir
2023-03-02 uhhhh here it is
2023-03-02 jesus duck
2023-03-02 initial website commit
2023-03-02 added gallery
2023-03-02 added gitignore
2023-03-02 fixed links
2023-03-02 added content to landing page
2023-04-10 meeting notes
2023-04-13 added meeting 20230328
2023-04-13 updated 2023-03-28 title card in logs.html
2023-04-13 fixed log.html template
2023-04-13 changed meeting log template.hmtl to follow 20230328.html format
2023-04-16 meeting today
2023-04-16 updated meeting note
2023-04-16 html meeting doc
2023-04-17 new meeting html for today 2023 04 17
2023-04-19 added stepperMotor.html for notes on stepper motor progress and info
2023-04-20 additional text to stepperMotor.html notes
2023-04-20 testing
2023-04-20 updated logs.html
2023-04-20 added github link
2023-04-20 oops
2023-04-20 added notes to stepperMotor.html
2023-05-04 resources added
2023-05-04 linkssss
2023-05-04 more links
2023-05-05 just added links.txt
2023-05-10 added links
2023-05-10 added info to links.txt
2023-05-11 croutons
2023-05-12 moved some files into notes folder and created image folder, put block diagram in there
2023-05-12 images added
2023-05-12 added final proposal pdf and zip
2023-05-12 added prototypeblockdiagram.png, updated gallery with images
2023-07-22 meeting 0722
2023-07-22 added meeting to meetings
2023-08-02 meeting 2023-08-02
2023-08-02 changed logs order to most-recent first
2023-08-02 formatting
2023-08-02 more minor formatting things
2023-08-17 added schematic pdf
2023-08-17 added meeting 2023 08 16
2023-08-17 added text to 08-09 meeting, forgot need to discuss
2023-08-17 added meetings to logs to update website
2023-08-17 forgot to change the names of the meeting cards on log, fixed
2023-08-19 Hardware v1.1 ready
2023-08-23 v1.2
2023-09-04 added stepper motor mount v1 stl and gcode
2023-09-06 added some page templates
2023-09-06 trying out the navbar script...
2023-09-06 more navbar updates
2023-09-06 more navbar changes, trying out dropdowns
2023-09-06 added navbar to all pages hopefully
2023-09-06 meeeeeting logs
2023-09-06 added more pages
2023-09-06 fixed broken nav link
2023-09-06 oops now there are two resources >:( fixed it
2023-09-06 added link to today's meeting
2023-09-06 more navbar script changes
2023-09-06 testing schedule template
2023-09-06 added milestone 2, testing to see visuals
2023-09-06 oopsie woopsie
2023-09-06 added milestones to schedule
2023-09-06 added pictures to images
2023-09-06 added more pics to images and testing fig captions in gallery
2023-09-06 added more pics to images, finished gallery
2023-09-06 added cards to members, dont know if will work tho
2023-09-06 picture
2023-09-06 added kinect library guide - needs improvement still probably
2023-09-08 cleaned up today meeting notes
2023-09-20 added meeting 9/19/2023 Tuesday
2023-10-31 added stepper motor mounts v2 stl and gcode files
2023-11-03 test gtk
2023-11-03 counterweight and cable clip gcode
2023-11-07 added non-working code (TagCoordinateSelector)
2023-11-07 added readme for software plans
2023-11-13 adding example-3 from gtk website with xml layout (builder.ui)
2023-11-13 create selector_v1.c and testing event presses using main.c template (i.e., no XML backing file)
2023-11-13 added main method code
2023-11-13 failed exe, fixed some warnings and errors, mainly syntax
2023-11-13 get position method not working
2023-11-13 selector_v1 compiles without warnings
2023-11-13 segmentation fault error
2023-11-13 movd fixed var to be global
2023-11-13 working key press events, need to change selector to grid
2023-11-13 trying drawing widget to simulate selector and grid space
2023-11-13 added drawing example
2023-11-13 testing drawing problems in test C file
2023-11-13 redid drawing and key press in test
2023-11-13 pressing key shows highlight, need to fix movement
2023-11-13 new attempt at test
2023-11-13 correct version to test
2023-11-13 snapping boxes work but need to fix how they snap to move in intervals
2023-11-13 removed selector_v1 executable
2023-11-13 created gtk-examples folder and moved example files to said folder
2023-11-13 new make file
2023-11-13 added snapping function to be in shorter intervals
2023-11-13 undoing changes
2023-11-13 floor to int?
2023-11-13 added boundaires so that the box doesn't go outside of the window view
2023-11-13 working part 1 (selector box) added comments and changed box to be transparent
2023-11-13 added images folder to become args for GUI eventually
2023-11-13 added enter key event to print selector box coordinates temporarily
2023-11-13 added command line args to open image file
2023-11-13 added full path to function
2023-11-13 plans to take images?
2023-11-14 sldfjldsf
2023-11-14 added counterweights again
2023-11-14 pic now showing when enter but stays with the selector
2023-11-14 changed makefile executable
2023-11-14 image now stays at coordinate when enter is pressed
2023-11-14 added flower image
2023-11-14 change make file executable to use flower image instead
2023-11-14 revert changes
2023-11-14 saving old code into test
2023-11-14 trying displaying the image in separate view on new branch
2023-11-14 added flags so that image only shows in the drawing area when entered, need to fix when entered again it disappears
2023-11-14 it shirnks ig..
2023-11-14 IMAGE SHRINKS NOW
2023-11-14 added coordinate text to terminal
2023-11-20 added stl for stepper motor mounts that include attachments to board functionality
2023-11-20 added gcode for stepper mounts v2
2023-11-20 drawable canvas :)
2023-11-20 more progress with signal routing
2023-11-21 more work on signal handlers, debugging now
2023-11-21 started gcode translator
2023-11-23 push from lab computer
2023-11-24 some gcode fixes
2023-11-25 added basic firmware
2023-11-25 half a firmware file
2023-11-25 firmware changes
2023-11-25 documentation, gear ratios
2023-11-25 added servo extender and pulley holder stl and gcode
2023-11-26 pseudo code for serial commands
2023-11-26 misc bugfixes, point transformation
2023-11-27 made testing files in py and c for serial comms to mimic our send_commands.c and main.ino
2023-11-27 fixed gcode to L/R
2023-11-28 makefile and header file changes
2023-11-29 started working on kinect integration, not working yet
2023-11-29 code written but immediately segfaults LMAO
2023-11-29 kinect tracking working! now integrate with switch buttons
2023-11-29 lots of progress with kinect + game controller, but problems with moving into selector stage
2023-11-29 lol fixed it
2023-11-30 nucleo breakout firmrware
2023-11-30 firmware working!
2023-12-02 last couple of changes here
2023-12-02 moved taggang prototype py code
2023-12-02 changed to py
2023-12-02 more serial work
2023-12-02 more working on serial
2023-12-02 SERIAL
2023-12-02 serial still not work
2023-12-02 segfault debug
2023-12-02 more segfault debug
2023-12-02 no more segfaults.... fingers crossed....
2023-12-02 pulled main-nucleo from main branch
2023-12-02 added debug folder to hold old serialsend code and moved mainserial to firmware
2023-12-02 debug files to hold old serial code to debug
2023-12-03 pulled more files from main
2023-12-03 pulled from main
2023-12-03 added debug temp file for send_commands
2023-12-03 transferring files from my laptop since pi is a slow ass bitch
2023-12-03 debug lines, is it sending properly?
2023-12-03 more debugging, not getting right buffer
2023-12-03 sending different buffer size
2023-12-03 send command debug script working
2023-12-03 wrong end char in debugging gcode
2023-12-03 removed newline for better data
2023-12-03 correct string being sent, but not receieving still in arduino
2023-12-03 debug print statements
2023-12-03 WORKING SERIALgit add . added lines of code that allows to read data from arduino
2023-12-03 pulled makefile from main
2023-12-03 deleted old files
2023-12-03 removed old code
2023-12-03 integrated sendcmd-debug.c file and added comments
2023-12-03 added comments
2023-12-03 changed widget lines to follow gcode.c
2023-12-04 refactoring, some more work needed to switch between screens though (widgets need to go in a Box)
2023-12-04 push to pi
2023-12-04 gui is workable
2023-12-04 misc debugging
2023-12-05 persistent drawings in selector stage
2023-12-05 more gui changes
2023-12-06 plotter works more or less!
2023-12-07 fixed gcoder
2023-12-07 we don't need to see all that
2023-12-07 merge
2023-12-07 updated todos
2023-12-08 plotter 3d prints
2023-12-08 firmware updates
2023-12-08 test
2023-12-08 testing debug
2023-12-08 copy from other device
2023-12-08 WORKING JOYCON SELECTOR
2023-12-08 comments
2023-12-08 condtion for new file
2023-12-08 changed
2023-12-08 testing displaying
2023-12-08 It Works
2023-12-08 merged main from debug-joycond
2023-12-08 Revert "merged main from debug-joycond"
    This reverts commit 2d69606d5d68dd96d8c4d2adecdceac5f5c999fa.
2023-12-08 Revert "It Works"
    This reverts commit 029b50be55894aee2d88405922ab15d503a73d48.
2023-12-08 added return
2023-12-08 changed back to window
2023-12-08 change
2023-12-12 saldjkfslkdfj
2023-12-12 laskdjflksadjfl
2023-12-17 website updates to fix dropdowns
2023-12-17 website updates to fix dropdowns part 2
2023-12-17 MORE dropdown !
2023-12-17 more dropdown debug
2023-12-20 added some images
2023-12-20 finished hardware page
2023-12-20 gcode.c

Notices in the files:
parts and their libraries:
SparkFun-Connectors: Licensing: Creative Commons ShareAlike 4.0 International - https://creativecommons.org/licenses/by-sa/4.0
